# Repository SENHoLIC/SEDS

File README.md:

#README

# Task 1: Finding the Sea Floor

Used Python to process the provided depth sensor CSV data.

## Approach

- Loaded and extracted the depth data using Pandas.
- Generated a time axis assuming one reading per second.
- Identified and handled noisy/abnormal readings.
- Plotted the processed depth against time using Matplotlib.

This helps visualize changes in depth and identifies potentially dangerous shallow regions.

---

# Task 2: Athena's Intern

Built an Arduino monitoring system in Tinkercad using a light sensor, ultrasonic sensor, push button, LCD, LED, and buzzer.

## Approach

- Used an LDR reading below `512` to detect **STORM**, with a blinking LED as the warning.
- Used an ultrasonic sensor to detect **CHARYBDIS** when an object is closer than `100 cm`, activating the buzzer.
- Used a push button to toggle the **ANCHOR DROPPED** state, protecting the ship from hazards.
- Implemented a state machine using `enum` and `switch` to manage **OPEN SEA**, **ANCHOR DROPPED**, **STORM**, **CHARYBDIS**, and **WRECKED**.
- Used `millis()` to track continuous danger and transition to **WRECKED** after `5 seconds`.
- Displayed the current state on the LCD.

This allows the system to continuously monitor hazards, respond to user input, and manage the ship's state automatically.

ThinkerCad Link: https://www.tinkercad.com/things/lly7G3LiDrp-athenas-intern-?sharecode=9iONrZv39ifyNwDU_UJ-KCoIgD_1QDnR-sug99MYklI

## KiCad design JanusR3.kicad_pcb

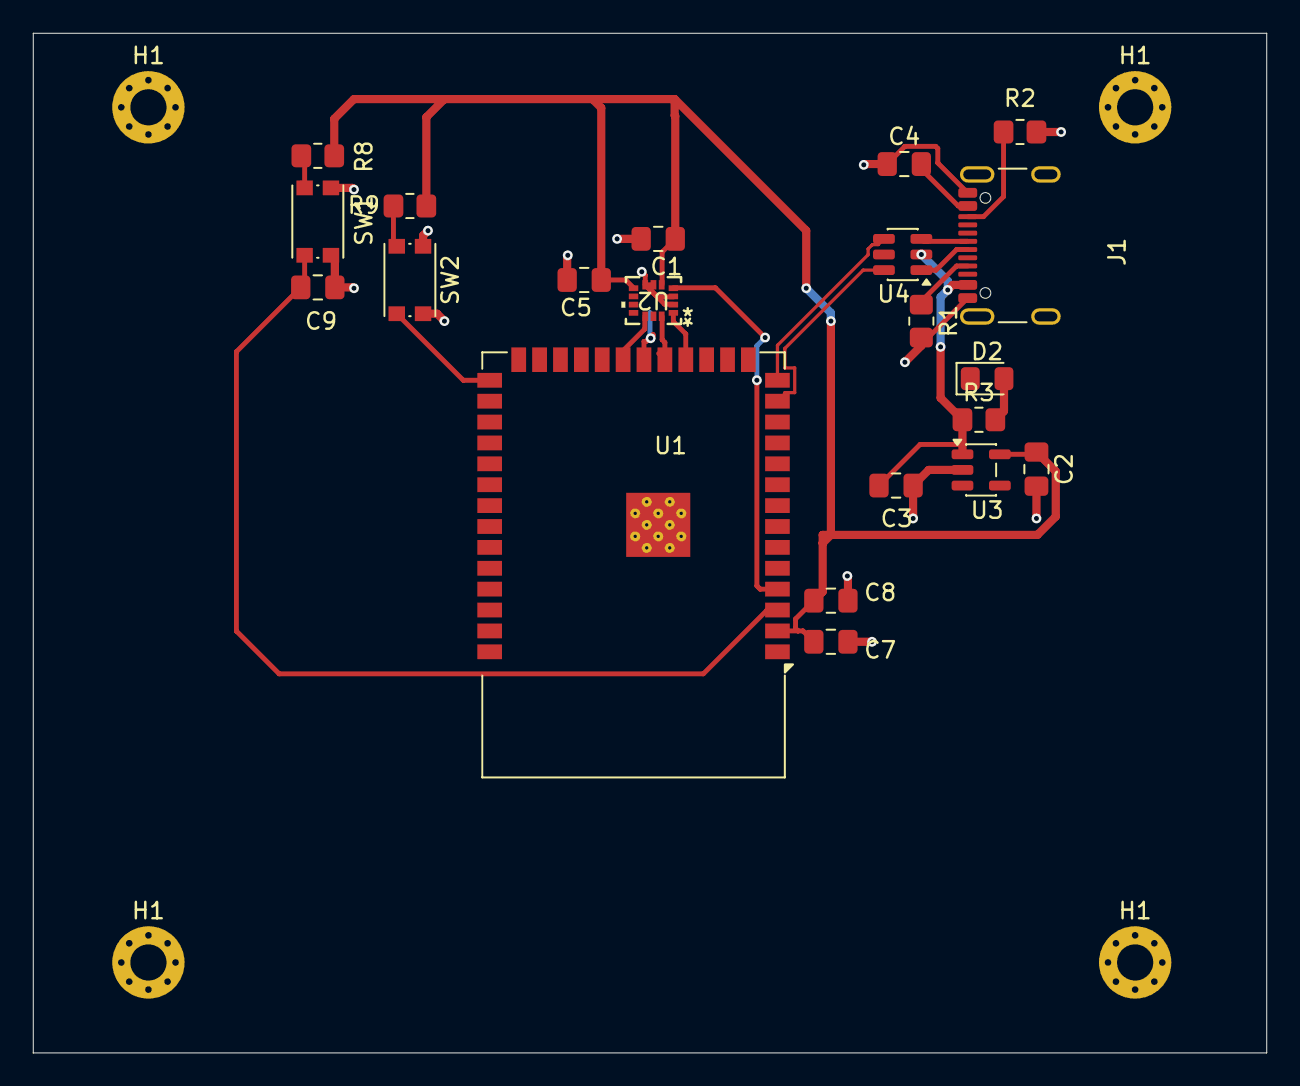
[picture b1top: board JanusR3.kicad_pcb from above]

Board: 2 copper layers, 75.0 x 62.0 mm, 25 parts (0 on the bottom side), 17 nets.

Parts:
C1, C4, C5: 100n; C_0805_2012Metric_Pad1.18x1.45mm_HandSolder
C2, C3, C9: 1u; C_0805_2012Metric_Pad1.18x1.45mm_HandSolder
C7: 100u; C_0805_2012Metric_Pad1.18x1.45mm_HandSolder
C8: 10u; C_0805_2012Metric_Pad1.18x1.45mm_HandSolder
D2: LED_Small; LED_0805_2012Metric_Pad1.15x1.40mm_HandSolder
H1, H1#2, H1#3, H1#4: MountingHole_Pad; MountingHole_2.2mm_M2_Pad_Via
J1: USB_C_Receptacle_USB2.0_16P; USB_C_Receptacle_GCT_USB4105-xx-A_16P_TopMnt_Horizontal
R1, R2: 5.1k; R_0805_2012Metric_Pad1.20x1.40mm_HandSolder
R3: 4.7k; R_0805_2012Metric_Pad1.20x1.40mm_HandSolder
R8, R9: 10k; R_0805_2012Metric_Pad1.20x1.40mm_HandSolder
SW1: RST_SW; SW_Push_1P1T_NO_CK_KMR2
SW2: BOOT_SW; SW_Push_1P1T_NO_CK_KMR2
U1: ESP32-S3-WROOM-1
U2: LSM6DSOTR; LGA-14L_2P5X3X0P86_STM
U3: TLV75733PDBV; SOT-23-5
U4: USBLC6-2SC6; SOT-23-6

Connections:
+3V3: C1.1, C2.1, C5.1, C7.1, C8.1, R8.1, R9.1, U1.2 (3V3), U2.5 (VDDIO), U2.8 (VDD), U3.5 (OUT)
BOOT: R9.2, SW2.2, U1.27 (IO0)
CS: U1.21 (IO13), U2.12 (CS)
D+: U1.13 (USB_D-), U4.6 (I/O1)
D+USB: J1.A6 (D+), J1.B6 (D+), U4.1 (I/O1)
D-: U1.14 (USB_D+), U4.4 (I/O2)
D-USB: J1.A7 (D-), J1.B7 (D-), U4.3 (I/O2)
GND: C1.2, C2.2, C3.2, C4.1, C5.2, C7.2, C8.2, C9.2, D2.1 (K), H1.1 (1_1), H1#2.1 (1_1), H1#3.1 (1_1), H1#4.1 (1_1), J1.A1 (GND), J1.A12 (GND), J1.B1 (GND), J1.B12 (GND), J1.SH (SHIELD), R1.2, R2.1, SW1.1, SW2.1, U1.1 (GND), U1.40 (GND), U1.41 (GND), U2.2 (SDx), U2.3 (SCx), U2.6 (GND), U2.7 (GND), U3.2 (GND), U4.5 (VBUS)
INT1: U1.4 (IO4), U2.4 (INT1)
MISO: U1.18 (IO10), U2.1 (SDO/SA0)
MOSI: U1.19 (IO11), U2.14 (SDA)
unnamed: D2.2 (A), R3.2
unnamed: J1.A5 (CC1), R1.1
unnamed: J1.B5 (CC2), R2.2
RST: C9.1, R8.2, SW1.2, U1.3 (EN)
SCK: U1.20 (IO12), U2.13 (SCL)
VBUS: C3.1, C4.2, J1.A4 (VBUS), J1.A9 (VBUS), J1.B4 (VBUS), J1.B9 (VBUS), R3.1, U3.1 (IN), U3.3 (EN), U4.2 (GND)
